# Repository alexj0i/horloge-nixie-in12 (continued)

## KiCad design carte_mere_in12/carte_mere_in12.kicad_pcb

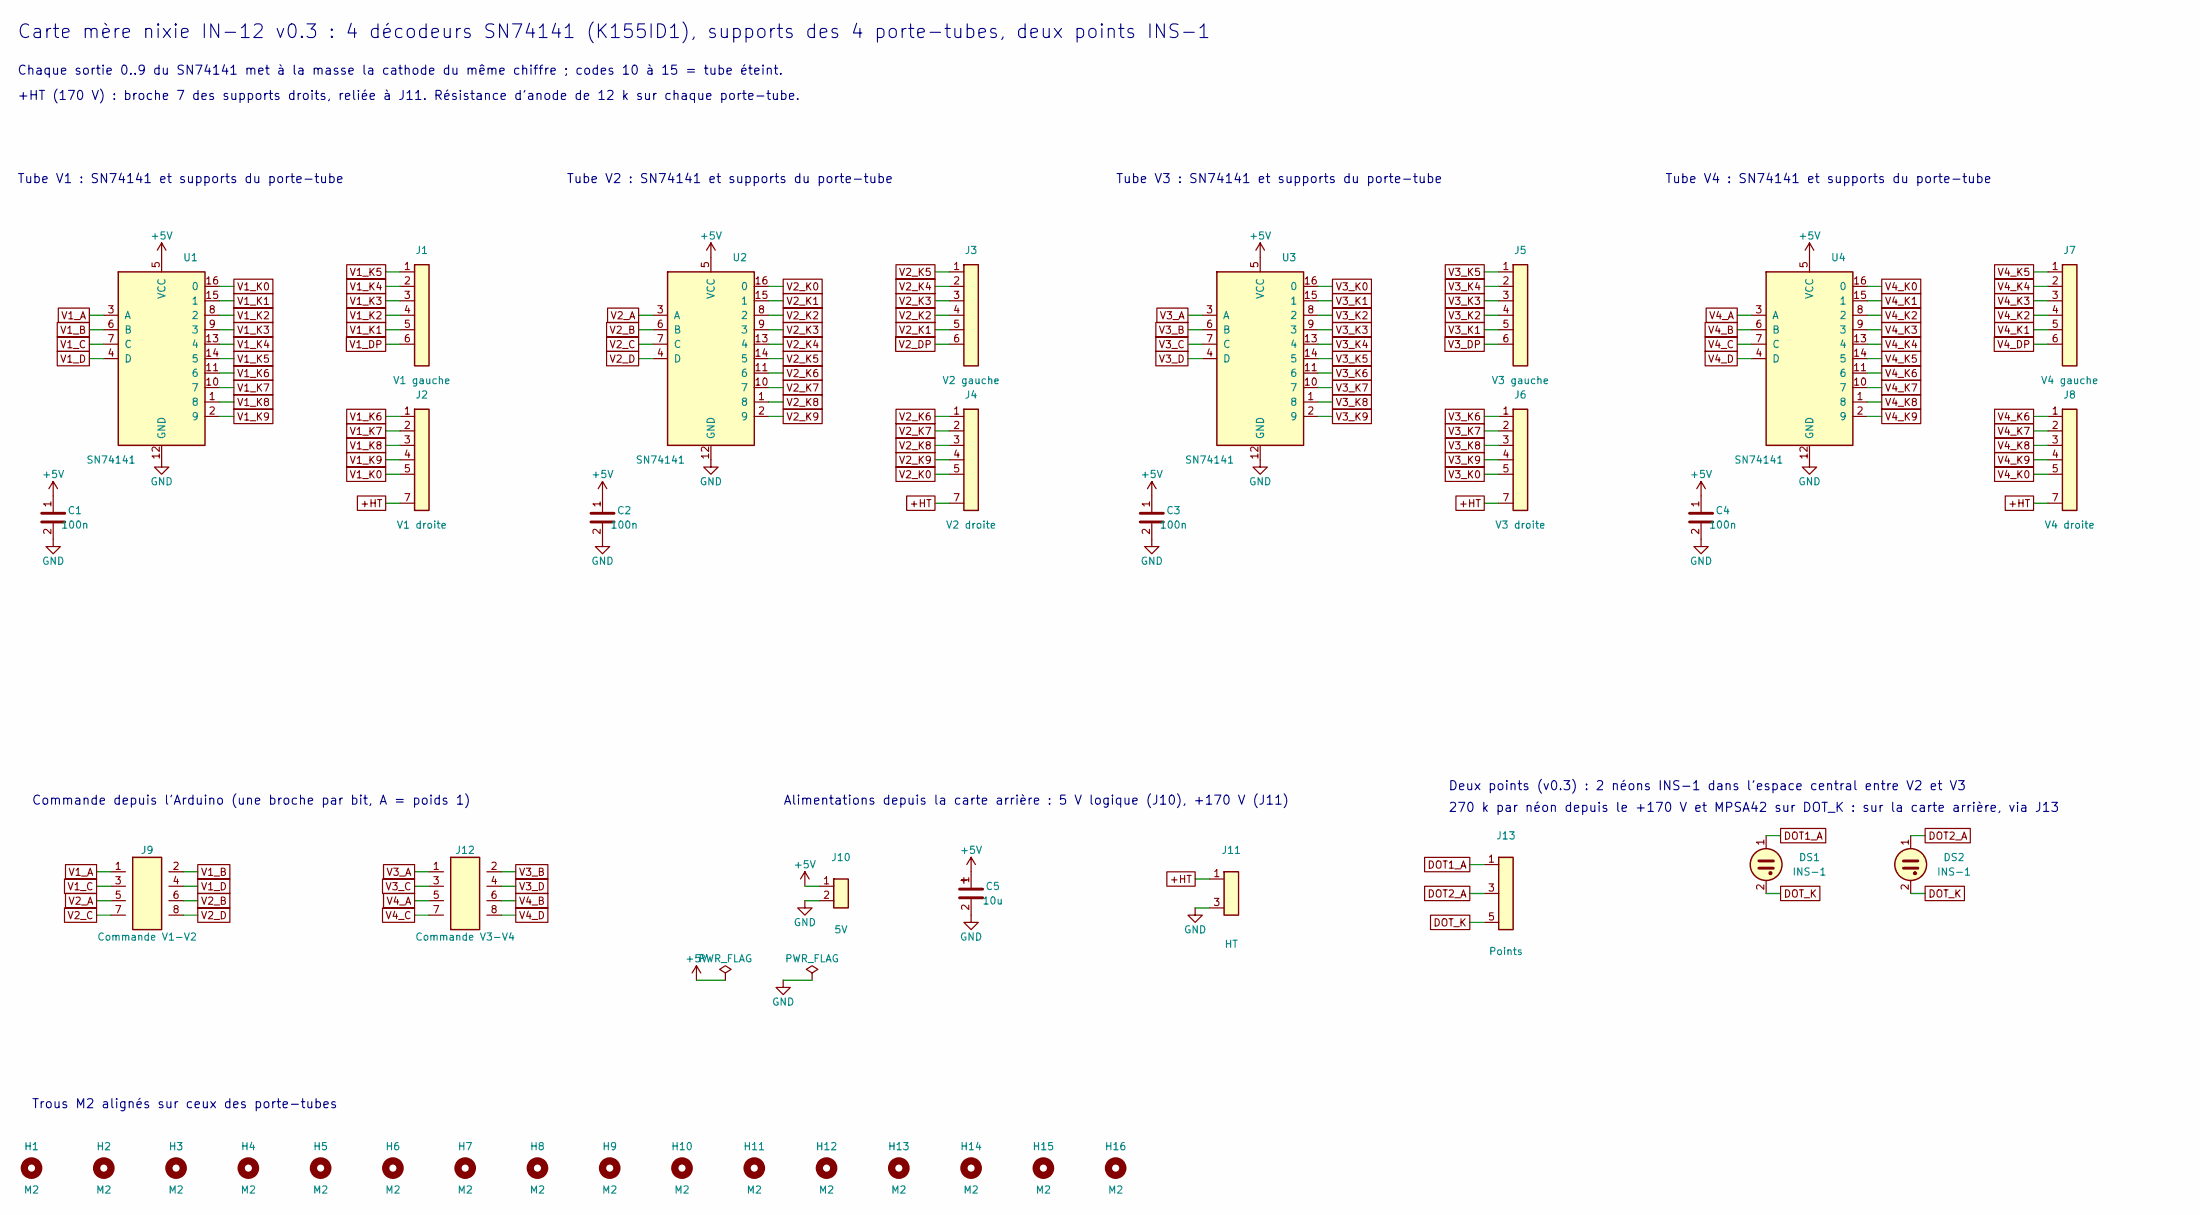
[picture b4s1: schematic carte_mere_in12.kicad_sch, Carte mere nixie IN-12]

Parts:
C1, C2, C3, C4: 100n; C_Disc_D3.0mm_W1.6mm_P2.50mm
C5: 10u; CP_Radial_D5.0mm_P2.00mm
DS1, DS2: INS-1; INS-1_P5.08mm
H1, H2, H3, H4, H5, H6, H7, H8, H9, H10, H11, H12, H13, H14, H15, H16: M2; MountingHole_2.2mm_M2
J1: V1 gauche; Support_1x07_Gauche
J2: V1 droite; Support_1x07_Droite
J3: V2 gauche; Support_1x07_Gauche
J4: V2 droite; Support_1x07_Droite
J5: V3 gauche; Support_1x07_Gauche
J6: V3 droite; Support_1x07_Droite
J7: V4 gauche; Support_1x07_Gauche
J8: V4 droite; Support_1x07_Droite
J9: Commande V1-V2; PinHeader_2x04_P2.54mm_Vertical
J10: 5V; PinHeader_1x02_P2.54mm_Vertical
J11: HT; HT_1x03_Cle2
J12: Commande V3-V4; PinHeader_2x04_P2.54mm_Vertical
J13: Points; Points_1x05_Cle24
U1, U2, U3, U4: SN74141; DIP-16_W7.62mm

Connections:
+5V: C1.1, C2.1, C3.1, C4.1, C5.1, J10.1, U1.5 (VCC), U2.5 (VCC), U3.5 (VCC), U4.5 (VCC)
+HT: J2.7, J4.7, J6.7, J8.7, J11.1
DOT1_A: DS1.1 (A), J13.1
DOT2_A: DS2.1 (A), J13.3
DOT_K: DS1.2 (K), DS2.2 (K), J13.5
GND: C1.2, C2.2, C3.2, C4.2, C5.2, J10.2, J11.3, U1.12 (GND), U2.12 (GND), U3.12 (GND), U4.12 (GND)
V1_A: J9.1, U1.3 (A)
V1_B: J9.2, U1.6 (B)
V1_C: J9.3, U1.7 (C)
V1_D: J9.4, U1.4 (D)
V1_DP: J1.6
V1_K0: J2.5, U1.16 (0)
V1_K1: J1.5, U1.15 (1)
V1_K2: J1.4, U1.8 (2)
V1_K3: J1.3, U1.9 (3)
V1_K4: J1.2, U1.13 (4)
V1_K5: J1.1, U1.14 (5)
V1_K6: J2.1, U1.11 (6)
V1_K7: J2.2, U1.10 (7)
V1_K8: J2.3, U1.1 (8)
V1_K9: J2.4, U1.2 (9)
V2_A: J9.5, U2.3 (A)
V2_B: J9.6, U2.6 (B)
V2_C: J9.7, U2.7 (C)
V2_D: J9.8, U2.4 (D)
V2_DP: J3.6
V2_K0: J4.5, U2.16 (0)
V2_K1: J3.5, U2.15 (1)
V2_K2: J3.4, U2.8 (2)
V2_K3: J3.3, U2.9 (3)
V2_K4: J3.2, U2.13 (4)
V2_K5: J3.1, U2.14 (5)
V2_K6: J4.1, U2.11 (6)
V2_K7: J4.2, U2.10 (7)
V2_K8: J4.3, U2.1 (8)
V2_K9: J4.4, U2.2 (9)
V3_A: J12.1, U3.3 (A)
V3_B: J12.2, U3.6 (B)
V3_C: J12.3, U3.7 (C)
V3_D: J12.4, U3.4 (D)
V3_DP: J5.6
V3_K0: J6.5, U3.16 (0)
V3_K1: J5.5, U3.15 (1)
V3_K2: J5.4, U3.8 (2)
V3_K3: J5.3, U3.9 (3)
V3_K4: J5.2, U3.13 (4)
V3_K5: J5.1, U3.14 (5)
V3_K6: J6.1, U3.11 (6)
V3_K7: J6.2, U3.10 (7)
V3_K8: J6.3, U3.1 (8)
V3_K9: J6.4, U3.2 (9)
V4_A: J12.5, U4.3 (A)
V4_B: J12.6, U4.6 (B)
V4_C: J12.7, U4.7 (C)
V4_D: J12.8, U4.4 (D)
V4_DP: J7.6
V4_K0: J8.5, U4.16 (0)
V4_K1: J7.5, U4.15 (1)
V4_K2: J7.4, U4.8 (2)
V4_K3: J7.3, U4.9 (3)
V4_K4: J7.2, U4.13 (4)
V4_K5: J7.1, U4.14 (5)
V4_K6: J8.1, U4.11 (6)
V4_K7: J8.2, U4.10 (7)
V4_K8: J8.3, U4.1 (8)
V4_K9: J8.4, U4.2 (9)

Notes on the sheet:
Tube V1 : SN74141 et supports du porte-tube
Tube V2 : SN74141 et supports du porte-tube
Tube V3 : SN74141 et supports du porte-tube
Tube V4 : SN74141 et supports du porte-tube
Commande depuis l'Arduino (une broche par bit, A = poids 1)
Alimentations depuis la carte arrière : 5 V logique (J10), +170 V (J11)
Deux points (v0.3) : 2 néons INS-1 dans l'espace central entre V2 et V3
270 k par néon depuis le +170 V et MPSA42 sur DOT_K : sur la carte arrière, via J13
Trous M2 alignés sur ceux des porte-tubes
Carte mère nixie IN-12 v0.3 : 4 décodeurs SN74141 (K155ID1), supports des 4 porte-tubes, deux points INS-1
Chaque sortie 0..9 du SN74141 met à la masse la cathode du même chiffre ; codes 10 à 15 = tube éteint.
+HT (170 V) : broche 7 des supports droits, reliée à J11. Résistance d'anode de 12 k sur chaque porte-tube.

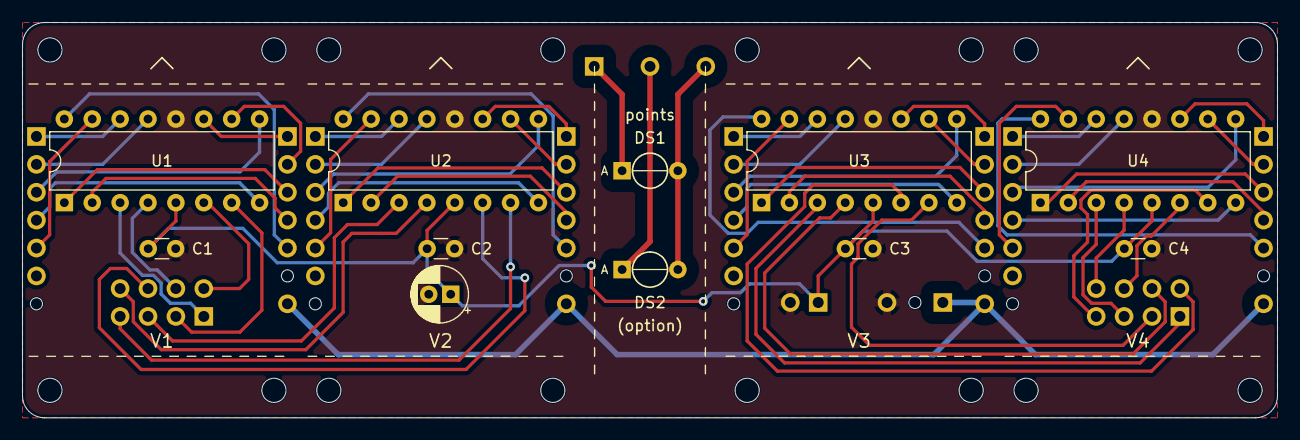
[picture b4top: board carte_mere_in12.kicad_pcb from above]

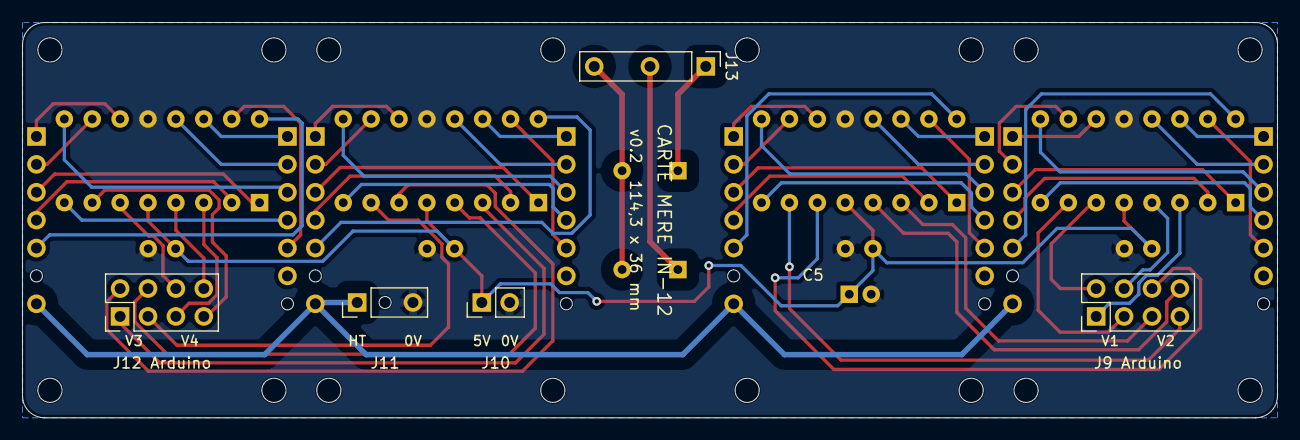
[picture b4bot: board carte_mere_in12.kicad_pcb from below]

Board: 2 copper layers, 114.3 x 36.0 mm, 40 parts (5 on the bottom side), 62 nets.
